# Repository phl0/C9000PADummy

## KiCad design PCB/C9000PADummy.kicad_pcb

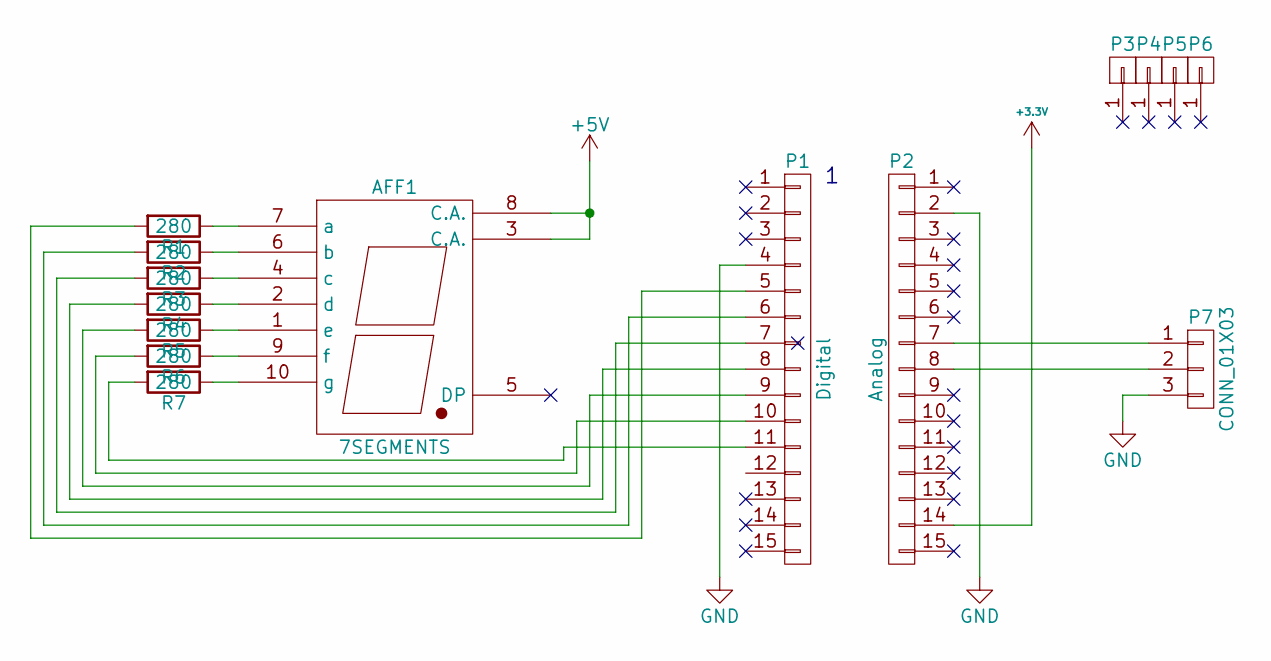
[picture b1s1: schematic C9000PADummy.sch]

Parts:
AFF1: 7SEGMENTS; 7SegmentLED_LTS6760_LTS6780
P1: Digital; Socket_Strip_Arduino_1x15
P2: Analog; Socket_Strip_Arduino_1x15
P3, P4, P5, P6: CONN_01X01; 1pin_Nano
P7: CONN_01X03; Pin_Header_Straight_1x03
R1, R2, R3, R4, R5, R6, R7: 280; Resistor_Horizontal_RM7mm

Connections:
+3V3: P2.14
+5V: AFF1.3 (C.A.), AFF1.8 (C.A.)
GND: P1.4, P2.2, P7.3
unnamed: AFF1.1 (e), R5.1
unnamed: AFF1.2 (d), R4.1
unnamed: AFF1.4 (c), R3.1
unnamed: AFF1.6 (b), R2.1
unnamed: AFF1.7 (a), R1.1
unnamed: AFF1.9 (f), R6.1
unnamed: AFF1.10 (g), R7.1
unnamed: P1.5, R1.2
unnamed: P1.6, R2.2
unnamed: P1.7, R3.2
unnamed: P1.8, R4.2
unnamed: P1.9, R5.2
unnamed: P1.10, R6.2
unnamed: P1.11, R7.2
unnamed: P2.7, P7.1
unnamed: P2.8, P7.2

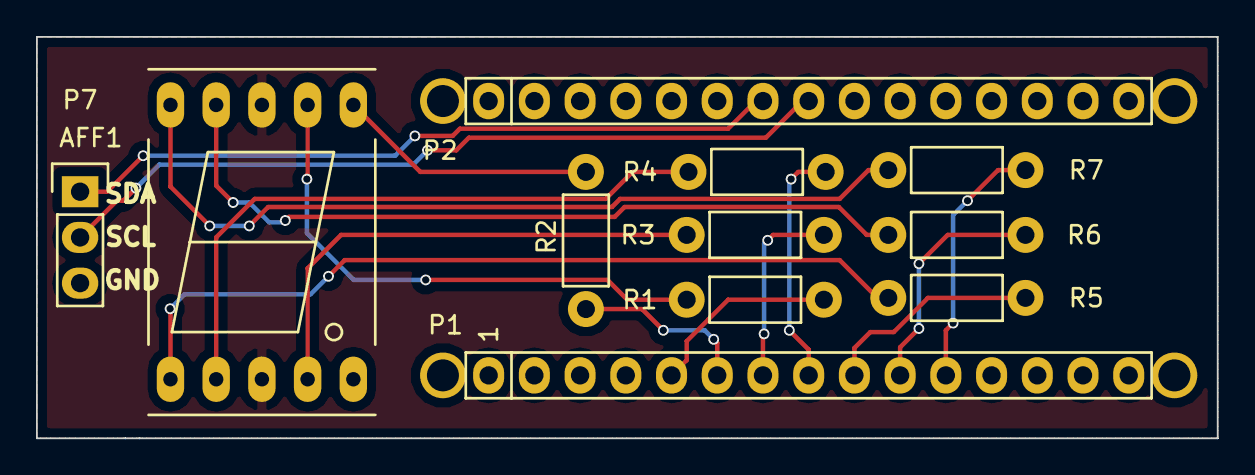
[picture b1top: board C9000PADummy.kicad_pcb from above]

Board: 2 copper layers, 65.6 x 22.3 mm, 15 parts (0 on the bottom side), 18 nets.

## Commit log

2017-08-15 Add PCB for 7-seg
